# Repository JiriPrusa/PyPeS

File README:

Modification of old Prusa i3 MK1 3D printer to automatic peptide synthesizer. There is a GUI in python that allows user to translate the synthesis steps into the commands for printer firmware (gcode). 3D models of syringe holder and eagle PCB design for servo motors driver.

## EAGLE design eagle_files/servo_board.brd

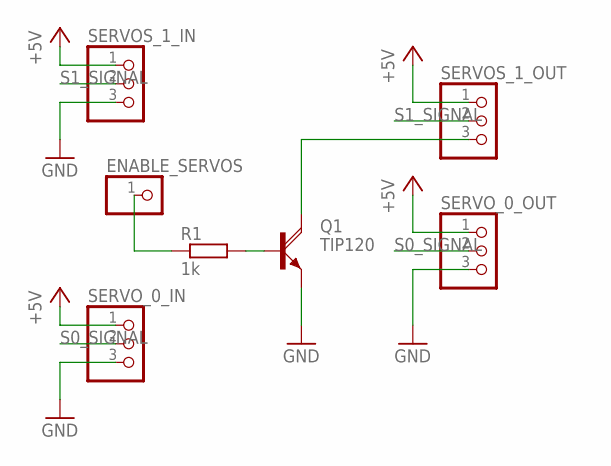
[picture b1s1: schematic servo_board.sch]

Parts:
ENABLE_SERVOS: PINHD-1X1; 1X01
Q1: TIP120; TO220AH
R1: 1k; 0204/5
SERVOS_1_IN, SERVOS_1_OUT: PINHD-1X3; 1X03
SERVO_0_IN, SERVO_0_OUT: PINHD-1X3; 1X03

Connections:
+5V: SERVOS_1_IN.1, SERVOS_1_OUT.1, SERVO_0_IN.1, SERVO_0_OUT.1
GND: Q1.E, SERVOS_1_IN.3, SERVO_0_IN.3, SERVO_0_OUT.3
unnamed: Q1.B, R1.2
unnamed: ENABLE_SERVOS.1, R1.1
unnamed: Q1.C, SERVOS_1_OUT.3
S0_SIGNAL: SERVO_0_IN.2, SERVO_0_OUT.2
S1_SIGNAL: SERVOS_1_IN.2, SERVOS_1_OUT.2

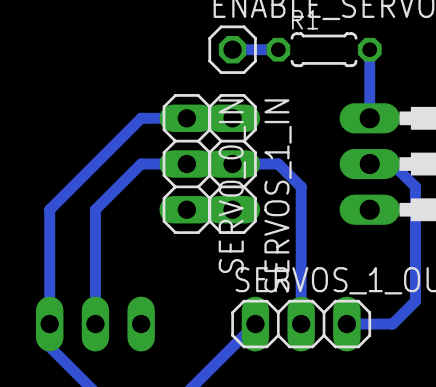
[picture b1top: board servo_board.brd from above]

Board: 2 copper layers, 7 parts (1 on the bottom side), 7 nets.

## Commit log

2022-11-04 initialization
